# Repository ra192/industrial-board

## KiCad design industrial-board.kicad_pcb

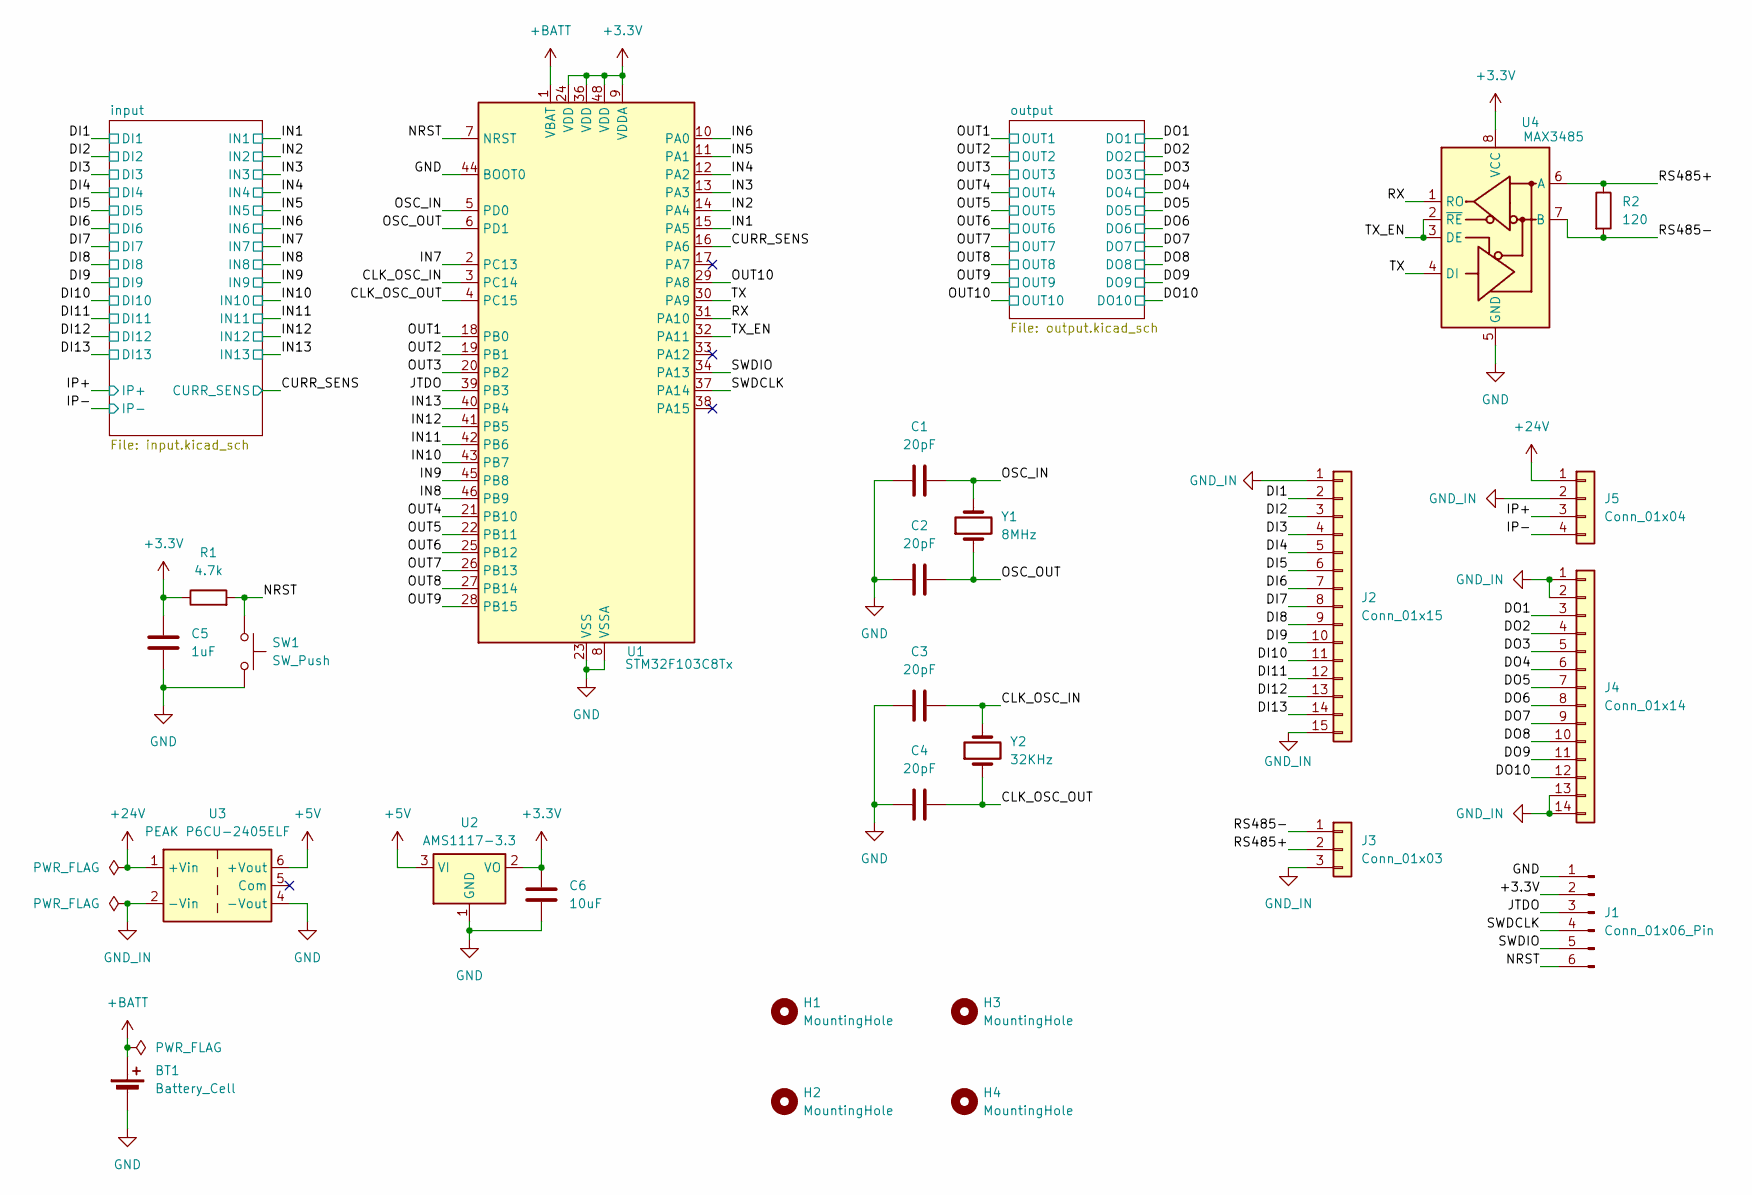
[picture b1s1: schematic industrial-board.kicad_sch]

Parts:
BT1: Battery_Cell; Battery_Panasonic_CR2032-VS1N_Vertical_CircularHoles
C1, C2, C3, C4: 20pF; C_0805_2012Metric_Pad1.18x1.45mm_HandSolder
C5: 1uF; C_0805_2012Metric_Pad1.18x1.45mm_HandSolder
C6: 10uF; C_0805_2012Metric_Pad1.18x1.45mm_HandSolder
H1, H2, H3, H4: MountingHole; MountingHole_3.2mm_M3
J1: Conn_01x06_Pin; PinHeader_1x06_P2.54mm_Vertical
J2: Conn_01x15; PhoenixContact_MCV_1,5_15-G-3.5_1x15_P3.50mm_Vertical
J3: Conn_01x03; PhoenixContact_MCV_1,5_3-G-3.5_1x03_P3.50mm_Vertical
J4: Conn_01x14; PhoenixContact_MCV_1,5_14-G-3.5_1x14_P3.50mm_Vertical
J5: Conn_01x04; PhoenixContact_MCV_1,5_4-G-3.5_1x04_P3.50mm_Vertical
R1: 4.7k; R_0805_2012Metric_Pad1.20x1.40mm_HandSolder
R2: 120; R_0805_2012Metric_Pad1.20x1.40mm_HandSolder
SW1: SW_Push; SW_SPST_B3S-1000
U1: STM32F103C8Tx; LQFP-48_7x7mm_P0.5mm
U2: AMS1117-3.3; SOT-223-3_TabPin2
U3: PEAK P6CU-2405ELF; Converter_DCDC_TRACO_TMA-15xxD_24xxD_Dual_THT
U4: MAX3485; SOIC-8_3.9x4.9mm_P1.27mm
Y1: 8MHz; Crystal_SMD_HC49-SD_HandSoldering
Y2: 32KHz; Crystal_AT310_D3.0mm_L10.0mm_Vertical

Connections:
+3.3V: C5.1, C6.1, J1.2, R1.1, U1.9 (VDDA), U1.24 (VDD), U1.36 (VDD), U1.48 (VDD), U2.2 (VO), U4.8 (VCC)
+5V: U2.3 (VI), U3.6 (+Vout); also elsewhere on the board
+24V: J5.1, U3.1 (+Vin); also elsewhere on the board
+BATT: BT1.1 (+), U1.1 (VBAT)
/CLK_OSC_IN: C3.2, U1.3 (PC14), Y2.2
/CLK_OSC_OUT: C4.2, U1.4 (PC15), Y2.1
/CURR_SENS: U1.16 (PA6); also elsewhere on the board
/DI1: J2.2; also elsewhere on the board
/DI2: J2.3; also elsewhere on the board
/DI3: J2.4; also elsewhere on the board
/DI4: J2.5; also elsewhere on the board
/DI5: J2.6; also elsewhere on the board
/DI6: J2.7; also elsewhere on the board
/DI7: J2.8; also elsewhere on the board
/DI8: J2.9; also elsewhere on the board
/DI9: J2.10; also elsewhere on the board
/DI10: J2.11; also elsewhere on the board
/DI11: J2.12; also elsewhere on the board
/DI12: J2.13; also elsewhere on the board
/DI13: J2.14; also elsewhere on the board
/DO1: J4.3; also elsewhere on the board
/DO2: J4.4; also elsewhere on the board
/DO3: J4.5; also elsewhere on the board
/DO4: J4.6; also elsewhere on the board
/DO5: J4.7; also elsewhere on the board
/DO6: J4.8; also elsewhere on the board
/DO7: J4.9; also elsewhere on the board
/DO8: J4.10; also elsewhere on the board
/DO9: J4.11; also elsewhere on the board
/DO10: J4.12; also elsewhere on the board
/IN1: U1.15 (PA5); also elsewhere on the board
/IN2: U1.14 (PA4); also elsewhere on the board
/IN3: U1.13 (PA3); also elsewhere on the board
/IN4: U1.12 (PA2); also elsewhere on the board
/IN5: U1.11 (PA1); also elsewhere on the board
/IN6: U1.10 (PA0); also elsewhere on the board
/IN7: U1.2 (PC13); also elsewhere on the board
/IN8: U1.46 (PB9); also elsewhere on the board
/IN9: U1.45 (PB8); also elsewhere on the board
/IN10: U1.43 (PB7); also elsewhere on the board
/IN11: U1.42 (PB6); also elsewhere on the board
/IN12: U1.41 (PB5); also elsewhere on the board
/IN13: U1.40 (PB4); also elsewhere on the board
/IP+: J5.3; also elsewhere on the board
/IP-: J5.4; also elsewhere on the board
/JTDO: J1.3, U1.39 (PB3)
/NRST: J1.6, R1.2, SW1.1, U1.7 (NRST)
/OSC_IN: C1.2, U1.5 (PD0), Y1.2
/OSC_OUT: C2.2, U1.6 (PD1), Y1.1
/OUT1: U1.18 (PB0); also elsewhere on the board
/OUT2: U1.19 (PB1); also elsewhere on the board
/OUT3: U1.20 (PB2); also elsewhere on the board
/OUT4: U1.21 (PB10); also elsewhere on the board
/OUT5: U1.22 (PB11); also elsewhere on the board
/OUT6: U1.25 (PB12); also elsewhere on the board
/OUT7: U1.26 (PB13); also elsewhere on the board
/OUT8: U1.27 (PB14); also elsewhere on the board
/OUT9: U1.28 (PB15); also elsewhere on the board
/OUT10: U1.29 (PA8); also elsewhere on the board
/RS485+: J3.2, R2.1, U4.6 (A)
/RS485-: J3.1, R2.2, U4.7 (B)
/RX: U1.31 (PA10), U4.1 (RO)
/SWDCLK: J1.4, U1.37 (PA14)
/SWDIO: J1.5, U1.34 (PA13)
/TX: U1.30 (PA9), U4.4 (DI)
/TX_EN: U1.32 (PA11), U4.2 (~RE), U4.3 (DE)
GND: BT1.2 (-), C1.1, C2.1, C3.1, C4.1, C5.2, C6.2, J1.1, SW1.2, U1.8 (VSSA), U1.23 (VSS), U1.35 (VSS), U1.44 (BOOT0), U1.47 (VSS), U2.1 (GND), U3.4 (-Vout), U4.5 (GND); also elsewhere on the board
GND_IN: J2.1, J2.15, J3.3, J4.1, J4.2, J4.13, J4.14, J5.2, U3.2 (-Vin); also elsewhere on the board

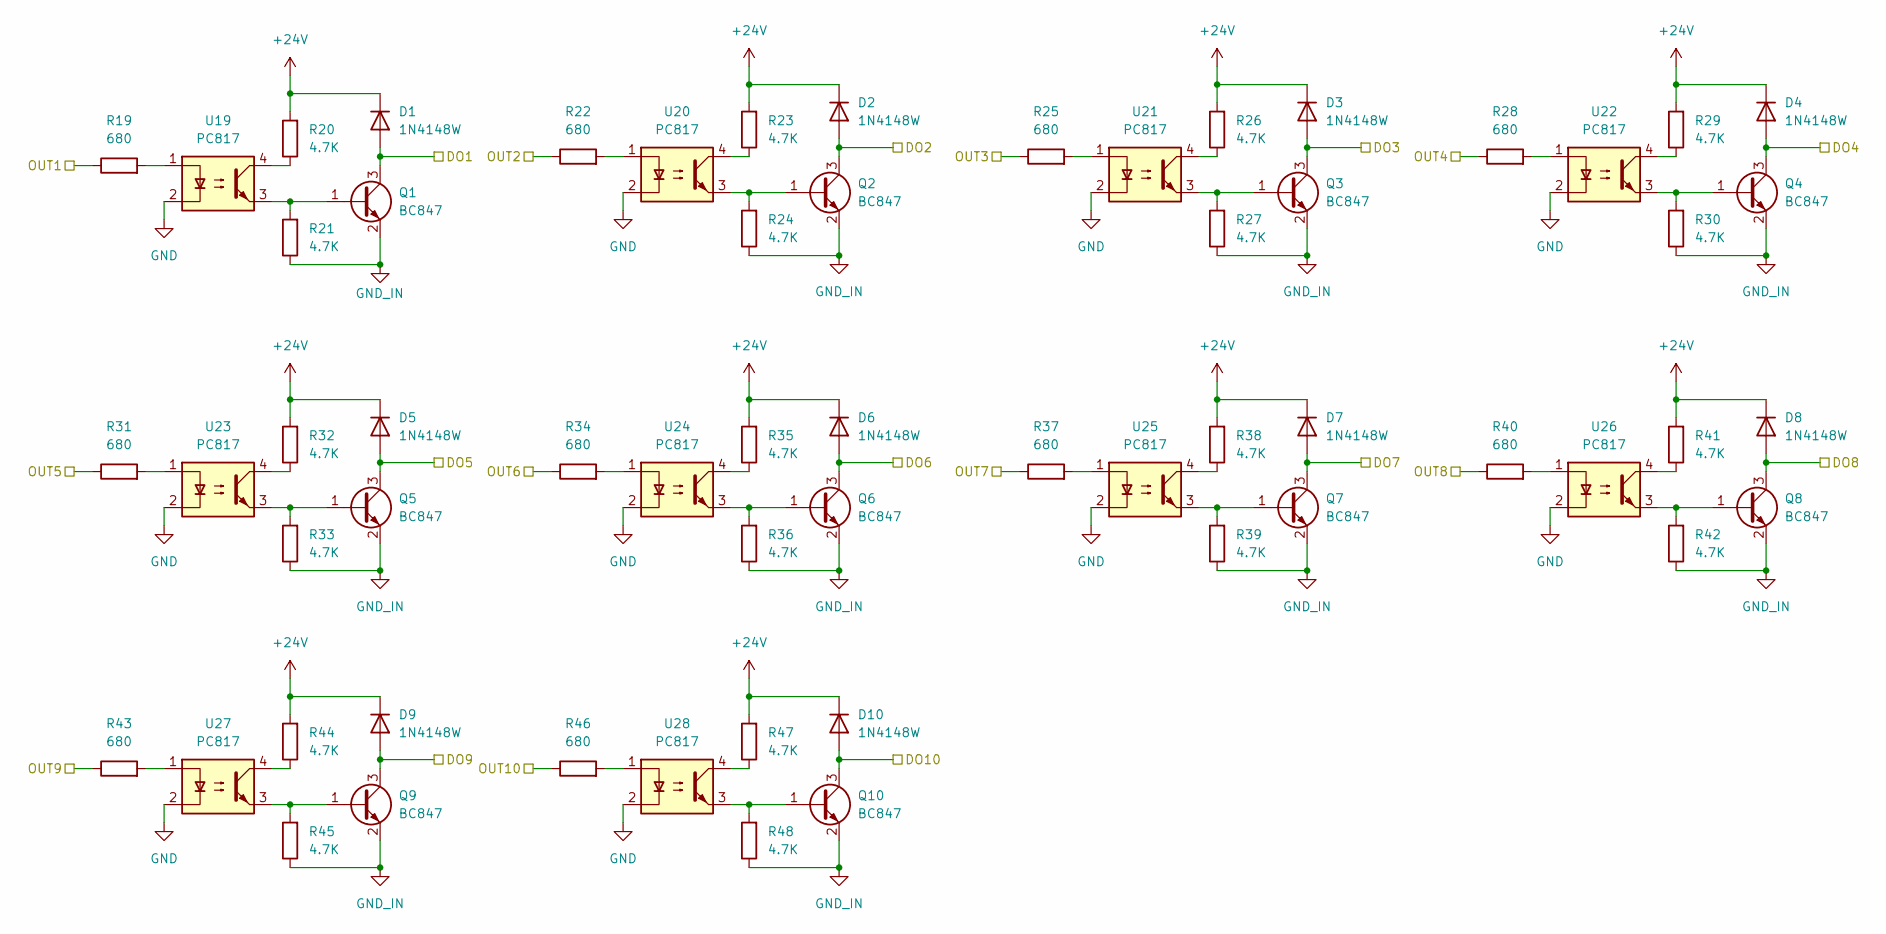
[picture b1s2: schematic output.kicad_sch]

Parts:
D1, D2, D3, D4, D5, D6, D7, D8, D9, D10: 1N4148W; D_SOD-123
Q1, Q2, Q3, Q4, Q5, Q6, Q7, Q8, Q9, Q10: BC847; SOT-23
R19, R22, R25, R28, R31, R34, R37, R40, R43, R46: 680; R_0805_2012Metric_Pad1.20x1.40mm_HandSolder
R20, R21, R23, R24, R26, R27, R29, R30, R32, R33, R35, R36, R38, R39, R41, R42, R44, R45, R47, R48: 4.7K; R_0805_2012Metric_Pad1.20x1.40mm_HandSolder
U19, U20, U21, U22, U23, U24, U25, U26, U27, U28: PC817; DIP-4_W7.62mm

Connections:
+24V: D1.1 (K), D2.1 (K), D3.1 (K), D4.1 (K), D5.1 (K), D6.1 (K), D7.1 (K), D8.1 (K), D9.1 (K), D10.1 (K), R20.2, R23.2, R26.2, R29.2, R32.2, R35.2, R38.2, R41.2, R44.2, R47.2; also elsewhere on the board
/DO1: D1.2 (A), Q1.3 (C); also elsewhere on the board
/DO2: D2.2 (A), Q2.3 (C); also elsewhere on the board
/DO3: D3.2 (A), Q3.3 (C); also elsewhere on the board
/DO4: D4.2 (A), Q4.3 (C); also elsewhere on the board
/DO5: D5.2 (A), Q5.3 (C); also elsewhere on the board
/DO6: D6.2 (A), Q6.3 (C); also elsewhere on the board
/DO7: D7.2 (A), Q7.3 (C); also elsewhere on the board
/DO8: D8.2 (A), Q8.3 (C); also elsewhere on the board
/DO9: D9.2 (A), Q9.3 (C); also elsewhere on the board
/DO10: D10.2 (A), Q10.3 (C); also elsewhere on the board
/OUT1: R19.1; also elsewhere on the board
/OUT2: R22.1; also elsewhere on the board
/OUT3: R25.1; also elsewhere on the board
/OUT4: R28.1; also elsewhere on the board
/OUT5: R31.1; also elsewhere on the board
/OUT6: R34.1; also elsewhere on the board
/OUT7: R37.1; also elsewhere on the board
/OUT8: R40.1; also elsewhere on the board
/OUT9: R43.1; also elsewhere on the board
/OUT10: R46.1; also elsewhere on the board
GND: U19.2, U20.2, U21.2, U22.2, U23.2, U24.2, U25.2, U26.2, U27.2, U28.2; also elsewhere on the board
GND_IN: Q1.2 (E), Q2.2 (E), Q3.2 (E), Q4.2 (E), Q5.2 (E), Q6.2 (E), Q7.2 (E), Q8.2 (E), Q9.2 (E), Q10.2 (E), R21.1, R24.1, R27.1, R30.1, R33.1, R36.1, R39.1, R42.1, R45.1, R48.1; also elsewhere on the board
unnamed: Q1.1 (B), R21.2, U19.3
unnamed: Q2.1 (B), R24.2, U20.3
unnamed: Q3.1 (B), R27.2, U21.3
unnamed: Q4.1 (B), R30.2, U22.3
unnamed: Q5.1 (B), R33.2, U23.3
unnamed: Q6.1 (B), R36.2, U24.3
unnamed: Q7.1 (B), R39.2, U25.3
unnamed: Q8.1 (B), R42.2, U26.3
unnamed: Q9.1 (B), R45.2, U27.3
unnamed: Q10.1 (B), R48.2, U28.3
unnamed: R19.2, U19.1
unnamed: R20.1, U19.4
unnamed: R22.2, U20.1
unnamed: R23.1, U20.4
unnamed: R25.2, U21.1
unnamed: R26.1, U21.4
unnamed: R28.2, U22.1
unnamed: R29.1, U22.4
unnamed: R31.2, U23.1
unnamed: R32.1, U23.4
unnamed: R34.2, U24.1
unnamed: R35.1, U24.4
unnamed: R37.2, U25.1
unnamed: R38.1, U25.4
unnamed: R40.2, U26.1
unnamed: R41.1, U26.4
unnamed: R43.2, U27.1
unnamed: R44.1, U27.4
unnamed: R46.2, U28.1
unnamed: R47.1, U28.4

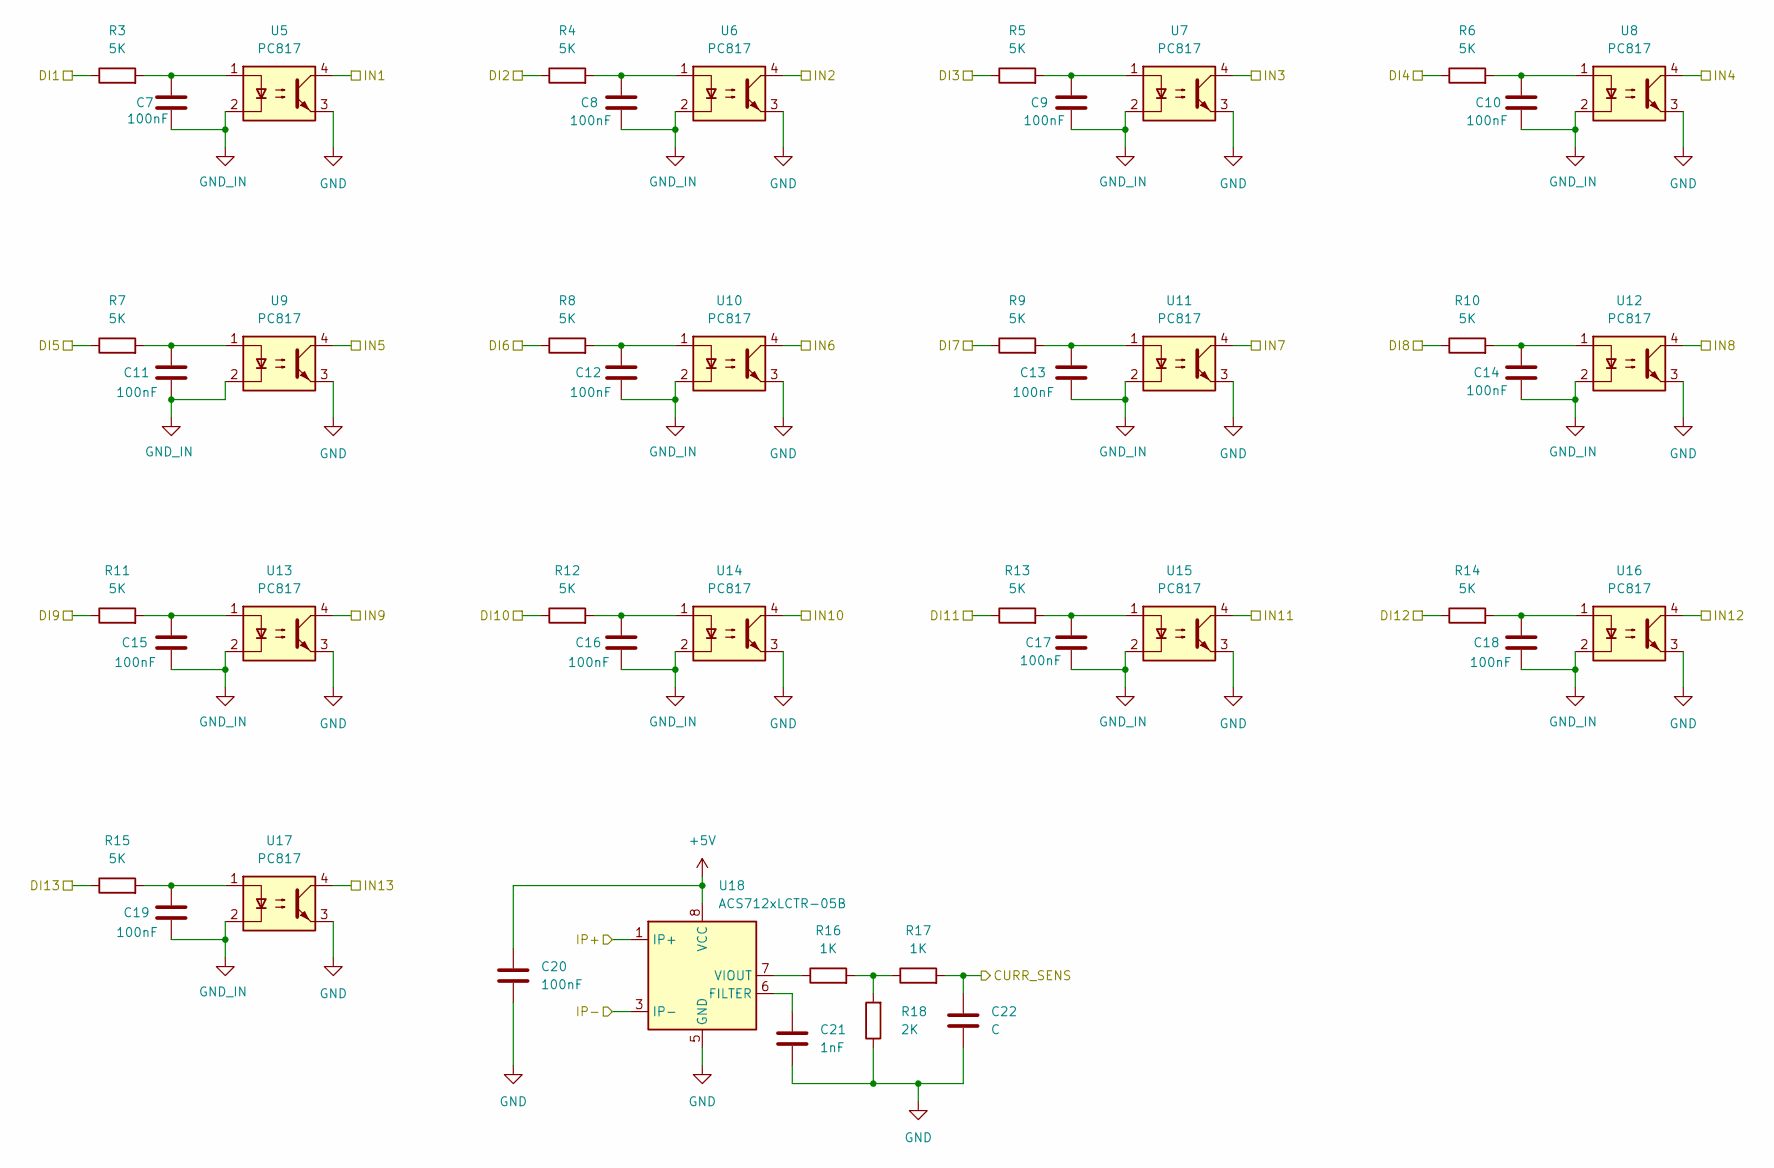
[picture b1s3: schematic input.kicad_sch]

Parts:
C7, C8, C9, C10, C11, C12, C13, C14, C15, C16, C17, C18, C19: 100nF; C_0805_2012Metric_Pad1.18x1.45mm_HandSolder
C20: 100nF; C_0805_2012Metric
C21: 1nF; C_0805_2012Metric
C22: C; C_0805_2012Metric
R3, R4, R5, R6, R7, R8, R9, R10, R11, R12, R13, R14, R15: 5K; R_0805_2012Metric_Pad1.20x1.40mm_HandSolder
R16, R17: 1K; R_0805_2012Metric_Pad1.20x1.40mm_HandSolder
R18: 2K; R_0805_2012Metric_Pad1.20x1.40mm_HandSolder
U5, U6, U7, U8, U9, U10, U11, U12, U13, U14, U15, U16, U17: PC817; DIP-4_W7.62mm
U18: ACS712xLCTR-05B; SOIC-8_3.9x4.9mm_P1.27mm

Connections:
+5V: C20.1, U18.8 (VCC); also elsewhere on the board
/CURR_SENS: C22.1, R17.2; also elsewhere on the board
/DI1: R3.1; also elsewhere on the board
/DI2: R4.1; also elsewhere on the board
/DI3: R5.1; also elsewhere on the board
/DI4: R6.1; also elsewhere on the board
/DI5: R7.1; also elsewhere on the board
/DI6: R8.1; also elsewhere on the board
/DI7: R9.1; also elsewhere on the board
/DI8: R10.1; also elsewhere on the board
/DI9: R11.1; also elsewhere on the board
/DI10: R12.1; also elsewhere on the board
/DI11: R13.1; also elsewhere on the board
/DI12: R14.1; also elsewhere on the board
/DI13: R15.1; also elsewhere on the board
/IN1: U5.4; also elsewhere on the board
/IN2: U6.4; also elsewhere on the board
/IN3: U7.4; also elsewhere on the board
/IN4: U8.4; also elsewhere on the board
/IN5: U9.4; also elsewhere on the board
/IN6: U10.4; also elsewhere on the board
/IN7: U11.4; also elsewhere on the board
/IN8: U12.4; also elsewhere on the board
/IN9: U13.4; also elsewhere on the board
/IN10: U14.4; also elsewhere on the board
/IN11: U15.4; also elsewhere on the board
/IN12: U16.4; also elsewhere on the board
/IN13: U17.4; also elsewhere on the board
/IP+: U18.1 (IP+), U18.2 (IP+); also elsewhere on the board
/IP-: U18.3 (IP-), U18.4 (IP-); also elsewhere on the board
GND: C20.2, C21.2, C22.2, R18.1, U5.3, U6.3, U7.3, U8.3, U9.3, U10.3, U11.3, U12.3, U13.3, U14.3, U15.3, U16.3, U17.3, U18.5 (GND); also elsewhere on the board
GND_IN: C7.2, C8.2, C9.2, C10.2, C11.2, C12.2, C13.2, C14.2, C15.2, C16.2, C17.2, C18.2, C19.2, U5.2, U6.2, U7.2, U8.2, U9.2, U10.2, U11.2, U12.2, U13.2, U14.2, U15.2, U16.2, U17.2; also elsewhere on the board
unnamed: C7.1, R3.2, U5.1
unnamed: C8.1, R4.2, U6.1
unnamed: C9.1, R5.2, U7.1
unnamed: C10.1, R6.2, U8.1
unnamed: C11.1, R7.2, U9.1
unnamed: C12.1, R8.2, U10.1
unnamed: C13.1, R9.2, U11.1
unnamed: C14.1, R10.2, U12.1
unnamed: C15.1, R11.2, U13.1
unnamed: C16.1, R12.2, U14.1
unnamed: C17.1, R13.2, U15.1
unnamed: C18.1, R14.2, U16.1
unnamed: C19.1, R15.2, U17.1
unnamed: R16.2, R17.1, R18.2
unnamed: C21.1, U18.6 (FILTER)
unnamed: R16.1, U18.7 (VIOUT)

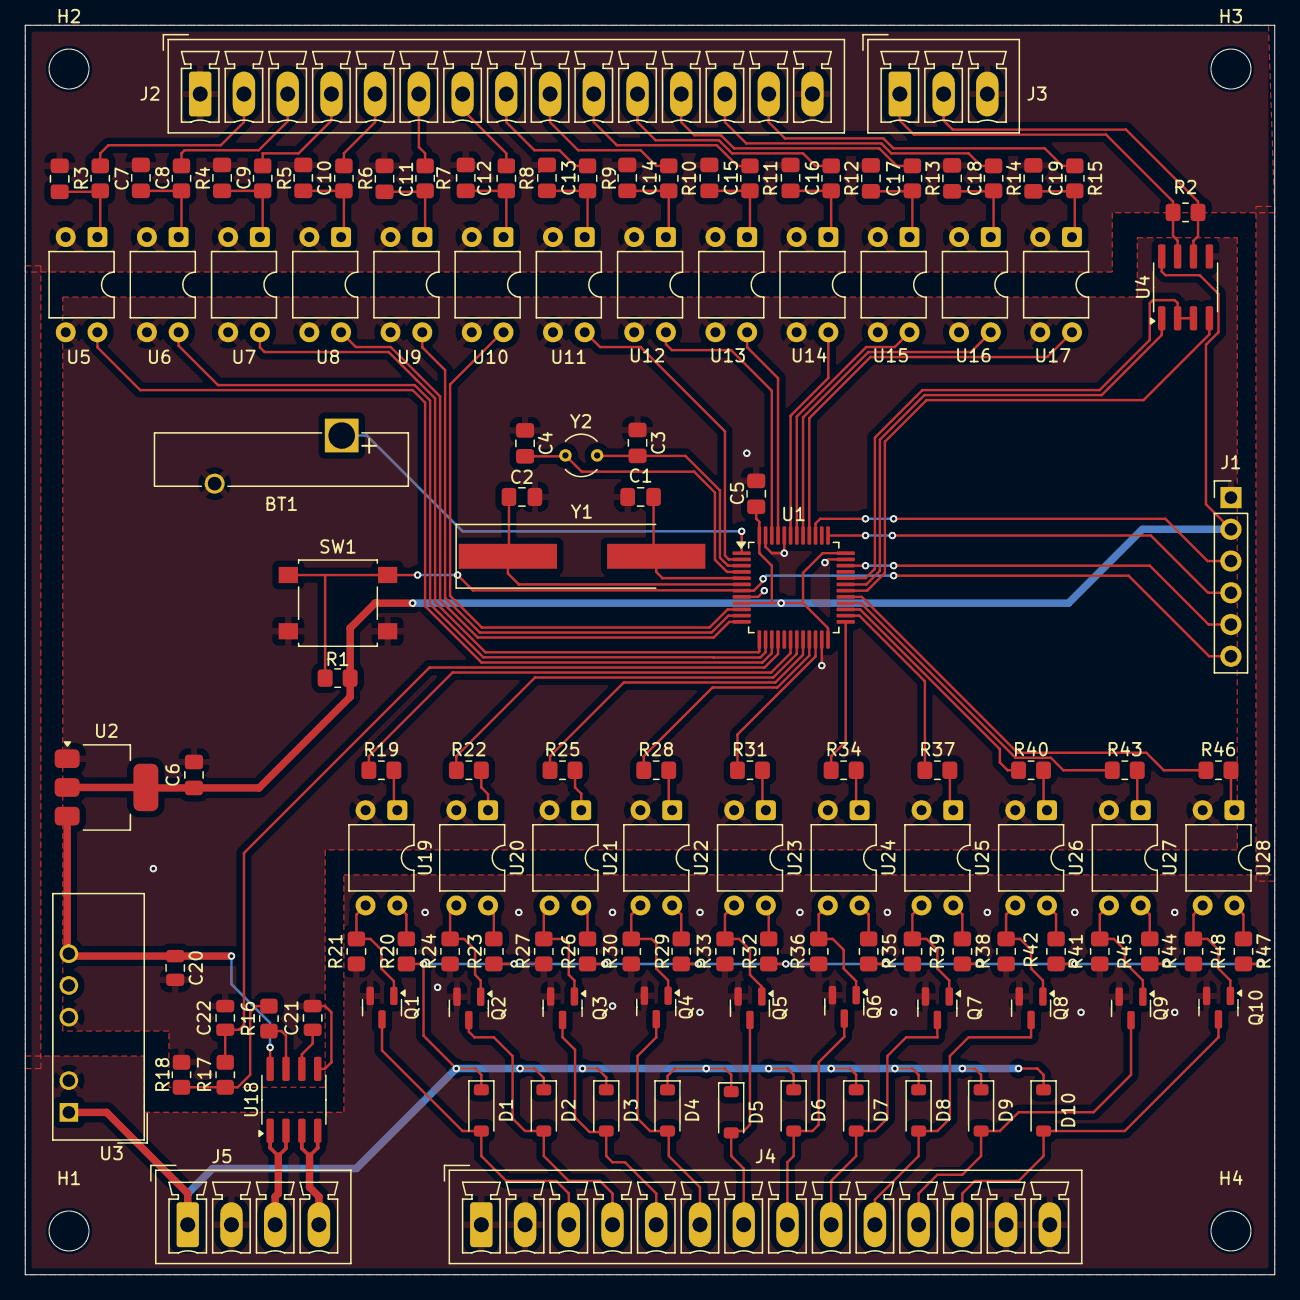
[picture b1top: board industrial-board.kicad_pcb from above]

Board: 2 copper layers, 100.0 x 100.0 mm, 131 parts (0 on the bottom side), 114 nets.

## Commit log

2025-01-14 change references
2025-01-15 minor changes
2025-01-16 add C values
2025-01-18 move components
2025-02-24 update project to kicad 9
2025-04-27 ground crystal oscillators
